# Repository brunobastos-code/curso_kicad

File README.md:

# curso_kicad
Arquivos do curso basico de Kicad

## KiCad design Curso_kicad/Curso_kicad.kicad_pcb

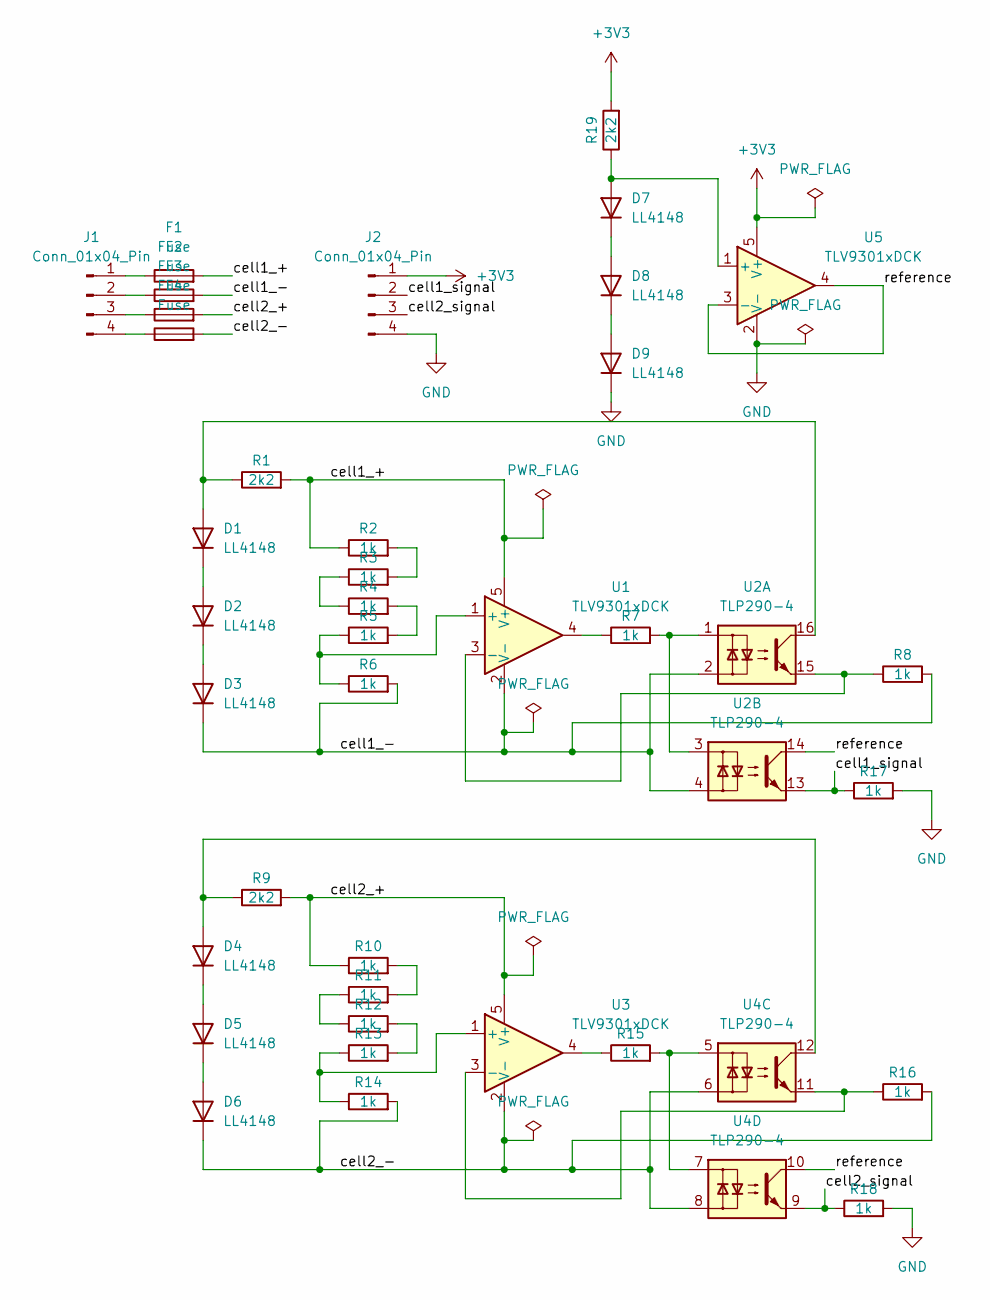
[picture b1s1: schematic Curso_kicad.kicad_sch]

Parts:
D1, D2, D3, D4, D5, D6, D7, D8, D9: LL4148; D_MiniMELF
F1, F2, F3, F4: Fuse; Fuse_1206_3216Metric
J1, J2: Conn_01x04_Pin; PinHeader_1x04_P2.54mm_Horizontal
R1, R9, R19: 2k2; R_0805_2012Metric
R2, R3, R4, R5, R6, R7, R8, R10, R11, R12, R13, R14, R15, R16, R17, R18: 1k; R_0805_2012Metric
U1, U3, U5: TLV9301xDCK; SOT-353_SC-70-5
U2, U4: TLP290-4; SOP-16_4.55x10.3mm_P1.27mm

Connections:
+3V3: J2.1, R19.2, U5.5 (V+)
/cell1_+: F1.2, R1.2, R2.1, U1.5 (V+)
/cell1_-: D3.1 (K), F2.2, R6.2, R8.2, U1.2 (V-), U2.2, U2.4
/cell1_signal: J2.2, R17.1, U2.13
/cell2_+: F3.2, R9.2, R10.1, U3.5 (V+)
/cell2_-: D6.1 (K), F4.2, R14.2, R16.2, U3.2 (V-), U4.6, U4.8
/cell2_signal: J2.3, R18.1, U4.9
/reference: U2.14, U4.10, U5.3 (-), U5.4
GND: D9.1 (K), J2.4, R17.2, R18.2, U5.2 (V-)
unnamed: D1.2 (A), R1.1, U2.16
unnamed: D1.1 (K), D2.2 (A)
unnamed: D2.1 (K), D3.2 (A)
unnamed: D4.2 (A), R9.1, U4.12
unnamed: D4.1 (K), D5.2 (A)
unnamed: D5.1 (K), D6.2 (A)
unnamed: D7.2 (A), R19.1, U5.1 (+)
unnamed: D7.1 (K), D8.2 (A)
unnamed: D8.1 (K), D9.2 (A)
unnamed: F1.1, J1.1
unnamed: F2.1, J1.2
unnamed: F3.1, J1.3
unnamed: F4.1, J1.4
unnamed: R2.2, R3.2
unnamed: R3.1, R4.1
unnamed: R4.2, R5.2
unnamed: R7.1, U1.4
unnamed: R7.2, U2.1, U2.3
unnamed: R10.2, R11.2
unnamed: R11.1, R12.1
unnamed: R12.2, R13.2
unnamed: R15.1, U3.4
unnamed: R15.2, U4.5, U4.7
unnamed: R5.1, R6.1, U1.1 (+)
unnamed: R8.1, U1.3 (-), U2.15
unnamed: R13.1, R14.1, U3.1 (+)
unnamed: R16.1, U3.3 (-), U4.11

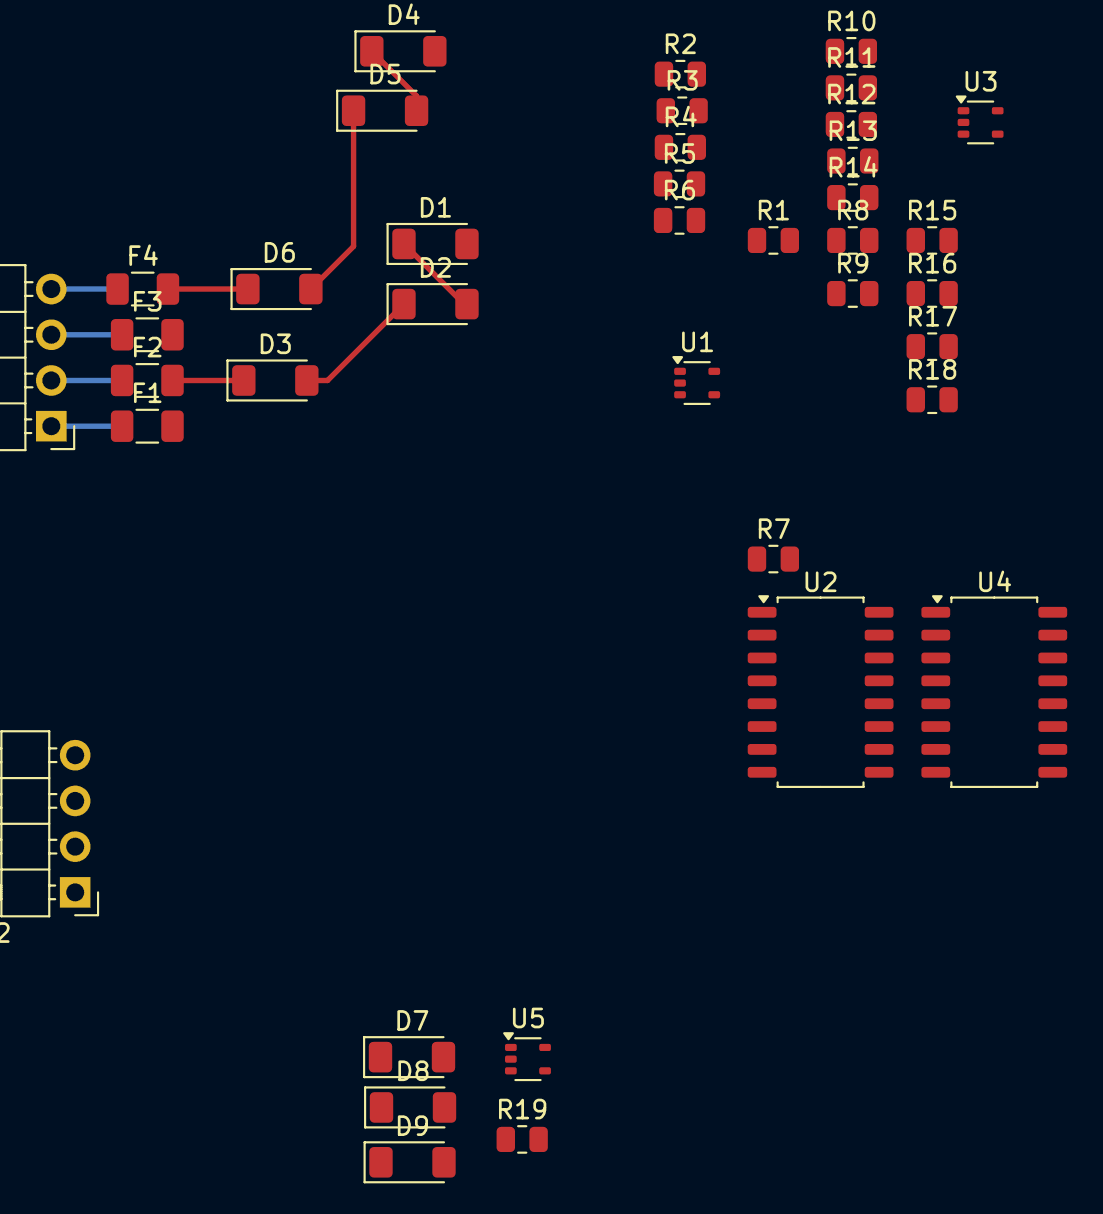
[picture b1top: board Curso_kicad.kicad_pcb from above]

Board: 2 copper layers, 39 parts (0 on the bottom side), 36 nets.

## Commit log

2024-07-01 Arquivos do curso basico de Kicad
